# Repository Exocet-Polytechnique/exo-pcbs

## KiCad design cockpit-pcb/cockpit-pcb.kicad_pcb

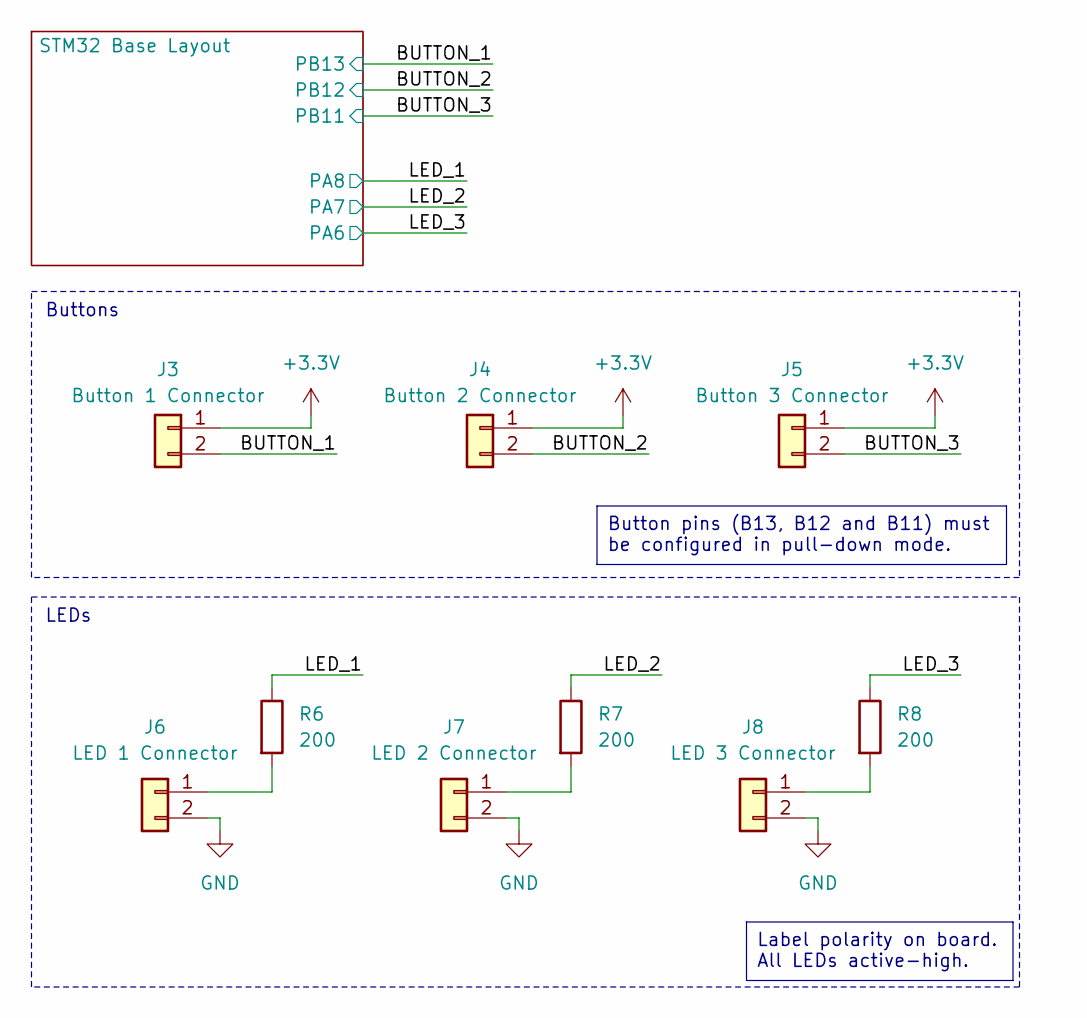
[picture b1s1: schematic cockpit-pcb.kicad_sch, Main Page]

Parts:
J3: Button 1 Connector; JST_ZH_B2B-ZR_1x02_P1.50mm_Vertical; JLCPCB C163033
J4: Button 2 Connector; JST_ZH_B2B-ZR_1x02_P1.50mm_Vertical; JLCPCB C163033
J5: Button 3 Connector; JST_ZH_B2B-ZR_1x02_P1.50mm_Vertical; JLCPCB C163033
J6: LED 1 Connector; JST_PH_B2B-PH-K_1x02_P2.00mm_Vertical; JLCPCB C131337
J7: LED 2 Connector; JST_PH_B2B-PH-K_1x02_P2.00mm_Vertical; JLCPCB C131337
J8: LED 3 Connector; JST_PH_B2B-PH-K_1x02_P2.00mm_Vertical; JLCPCB C131337
R6, R7, R8: 200; R_0603_1608Metric; JLCPCB C8218

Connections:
+3.3V: J3.1, J4.1, J5.1; also elsewhere on the board
/BUTTON_1: J3.2; also elsewhere on the board
/BUTTON_2: J4.2; also elsewhere on the board
/BUTTON_3: J5.2; also elsewhere on the board
/LED_1: R6.1; also elsewhere on the board
/LED_2: R7.1; also elsewhere on the board
/LED_3: R8.1; also elsewhere on the board
GND: J6.2, J7.2, J8.2; also elsewhere on the board
unnamed: J6.1, R6.2
unnamed: J7.1, R7.2
unnamed: J8.1, R8.2

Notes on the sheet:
LEDs
Buttons
Label polarity on board. All LEDs active-high.
Button pins (B13, B12 and B11) must be configured in pull-down mode.

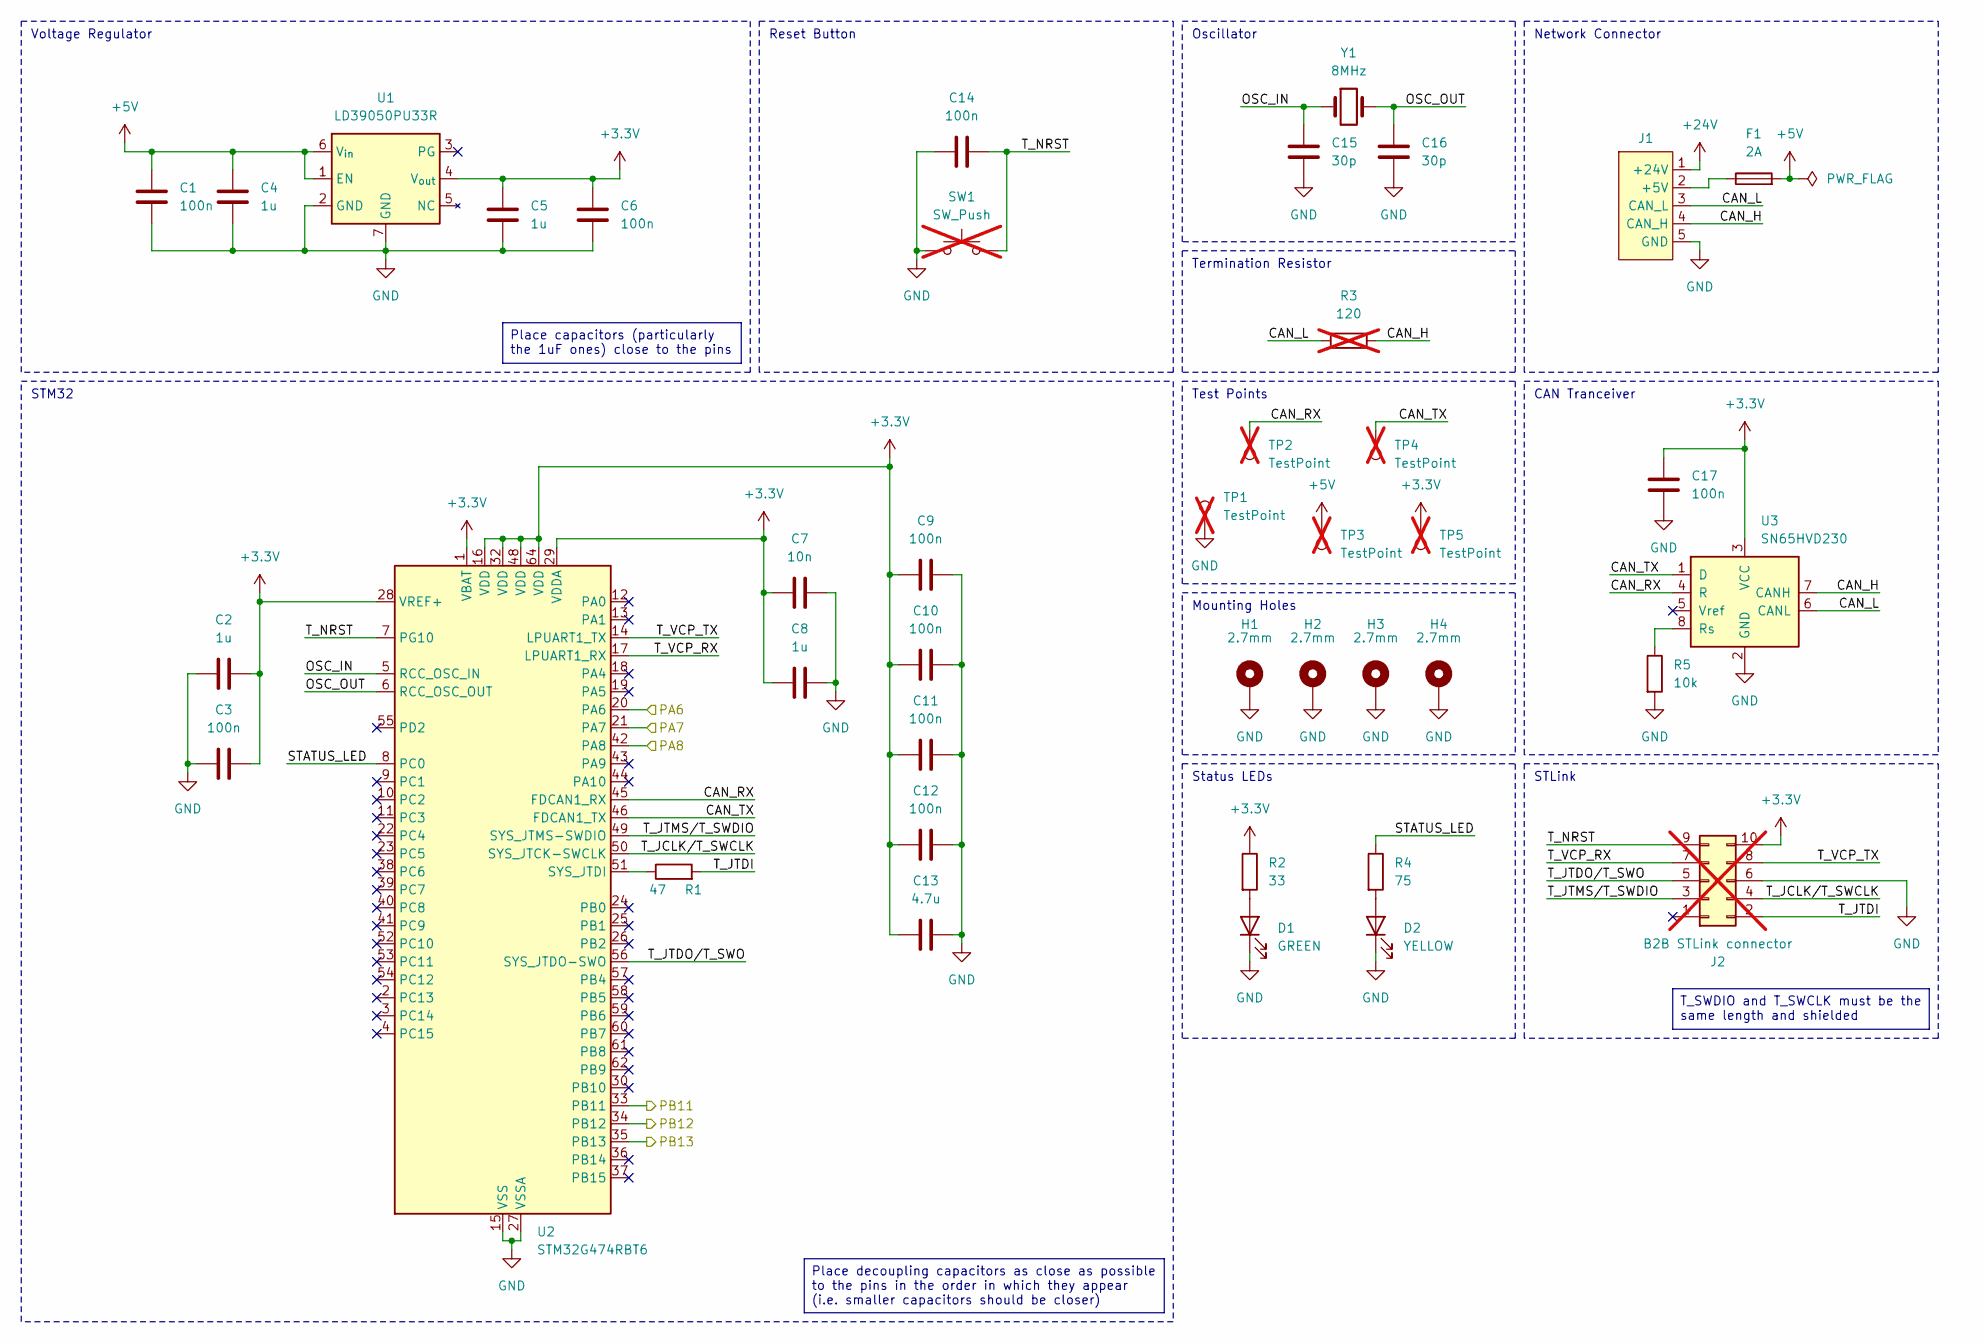
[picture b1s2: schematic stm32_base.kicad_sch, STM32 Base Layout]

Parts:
C1, C3, C6, C9, C10, C11, C12, C14, C17: 100n; C_0402_1005Metric; JLCPCB C1525
C2, C4, C5, C8: 1u; C_0603_1608Metric; JLCPCB C15849
C7: 10n; C_0603_1608Metric; JLCPCB C57112
C13: 4.7u; C_0603_1608Metric; JLCPCB C19666
C15, C16: 30p; C_0603_1608Metric; JLCPCB C1658
D1: GREEN; LED_0805_2012Metric_With_Annotations; JLCPCB C2297
D2: YELLOW; LED_0805_2012Metric_With_Annotations; JLCPCB C2296
F1: 2A; Fuse_Holder_Littelfuse_01530008; JLCPCB C206907
H1, H2, H3, H4: 2.7mm; MountingHole_2.7mm_Pad
J1: Network Connector; Molex_SPOX_5268-05A_1x05_P2.50mm_Horizontal; JLCPCB C185201
J2: B2B STLink connector; AVX 00-9159-010-BTB Connector; not fitted
R1: 47; R_0603_1608Metric; JLCPCB C23182
R2: 33; R_0603_1608Metric; JLCPCB C23140
R3: 120; R_Axial_DIN0309_L9.0mm_D3.2mm_P12.70mm_Horizontal; not fitted
R4: 75; R_0603_1608Metric; JLCPCB C4275
R5: 10k; R_0603_1608Metric; JLCPCB C25804
SW1: SW_Push; SW_PUSH_6mm; not fitted
TP1, TP2, TP3, TP4, TP5: TestPoint; TestPoint_Keystone_5005-5009_Compact; not fitted
U1: LD39050PU33R; DFN-6-1EP_3x3mm_P0.95mm_EP1.7x2.6mm; JLCPCB C132827
U2: STM32G474RBT6; LQFP-64_10x10mm_P0.5mm; JLCPCB C529413
U3: SN65HVD230; SOIC-8_3.9x4.9mm_P1.27mm; JLCPCB C12084
Y1: 8MHz; Crystal_SMD_HC49-SD; Part Name X49SM8MSD2SC; JLCPCB C12674

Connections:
+3.3V: C2.2, C3.2, C5.1, C6.1, C7.1, C8.1, C9.1, C10.1, C11.1, C12.1, C13.1, C17.1, J2.10, R2.1, TP5.1, U1.4 (V_{out}), U2.1 (VBAT), U2.16 (VDD), U2.28 (VREF+), U2.29 (VDDA), U2.32 (VDD), U2.48 (VDD), U2.64 (VDD), U3.3 (VCC); also elsewhere on the board
+5V: C1.1, C4.1, F1.2, TP3.1, U1.1 (EN), U1.6 (V_{in})
+24V: J1.1 (+24V)
/BUTTON_1: U2.35 (PB13); also elsewhere on the board
/BUTTON_2: U2.34 (PB12); also elsewhere on the board
/BUTTON_3: U2.33 (PB11); also elsewhere on the board
/LED_1: U2.42 (PA8); also elsewhere on the board
/LED_2: U2.21 (PA7); also elsewhere on the board
/LED_3: U2.20 (PA6); also elsewhere on the board
/STM32 Base Layout/CAN_H: J1.4 (CAN_H), R3.2, U3.7 (CANH)
/STM32 Base Layout/CAN_L: J1.3 (CAN_L), R3.1, U3.6 (CANL)
/STM32 Base Layout/CAN_RX: TP2.1, U2.45 (FDCAN1_RX), U3.4 (R)
/STM32 Base Layout/CAN_TX: TP4.1, U2.46 (FDCAN1_TX), U3.1 (D)
/STM32 Base Layout/OSC_IN: C15.1, U2.5 (RCC_OSC_IN), Y1.1
/STM32 Base Layout/OSC_OUT: C16.1, U2.6 (RCC_OSC_OUT), Y1.2
/STM32 Base Layout/STATUS_LED: R4.1, U2.8 (PC0)
/STM32 Base Layout/T_JCLK/T_SWCLK: J2.4, U2.50 (SYS_JTCK-SWCLK)
/STM32 Base Layout/T_JTDI: J2.2, R1.2
/STM32 Base Layout/T_JTDO/T_SWO: J2.5, U2.56 (SYS_JTDO-SWO)
/STM32 Base Layout/T_JTMS/T_SWDIO: J2.3, U2.49 (SYS_JTMS-SWDIO)
/STM32 Base Layout/T_NRST: C14.2, J2.9, SW1.2, U2.7 (PG10)
/STM32 Base Layout/T_VCP_RX: J2.7, U2.17 (LPUART1_RX)
/STM32 Base Layout/T_VCP_TX: J2.8, U2.14 (LPUART1_TX)
GND: C1.2, C2.1, C3.1, C4.2, C5.2, C6.2, C7.2, C8.2, C9.2, C10.2, C11.2, C12.2, C13.2, C14.1, C15.2, C16.2, C17.2, D1.1 (K), D2.1 (K), H1.1, H2.1, H3.1, H4.1, J1.5 (GND), J2.6, R5.2, SW1.1, TP1.1, U1.2 (GND), U1.7 (GND), U2.15 (VSS), U2.27 (VSSA), U2.31 (VSS), U2.47 (VSS), U2.63 (VSS), U3.2 (GND); also elsewhere on the board
unnamed: D1.2 (A), R2.2
unnamed: D2.2 (A), R4.2
unnamed: F1.1, J1.2 (+5V)
unnamed: R1.1, U2.51 (SYS_JTDI)
unnamed: R5.1, U3.8 (Rs)

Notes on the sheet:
CAN Tranceiver
Mounting Holes
Voltage Regulator
Reset Button
Status LEDs
Termination Resistor
Oscillator
STLink
Test Points
Network Connector
STM32
T_SWDIO and T_SWCLK must be the same length and shielded
Place capacitors (particularly the 1uF ones) close to the pins
Place decoupling capacitors as close as possible to the pins in the order in which they appear (i.e. smaller capacitors should be closer)

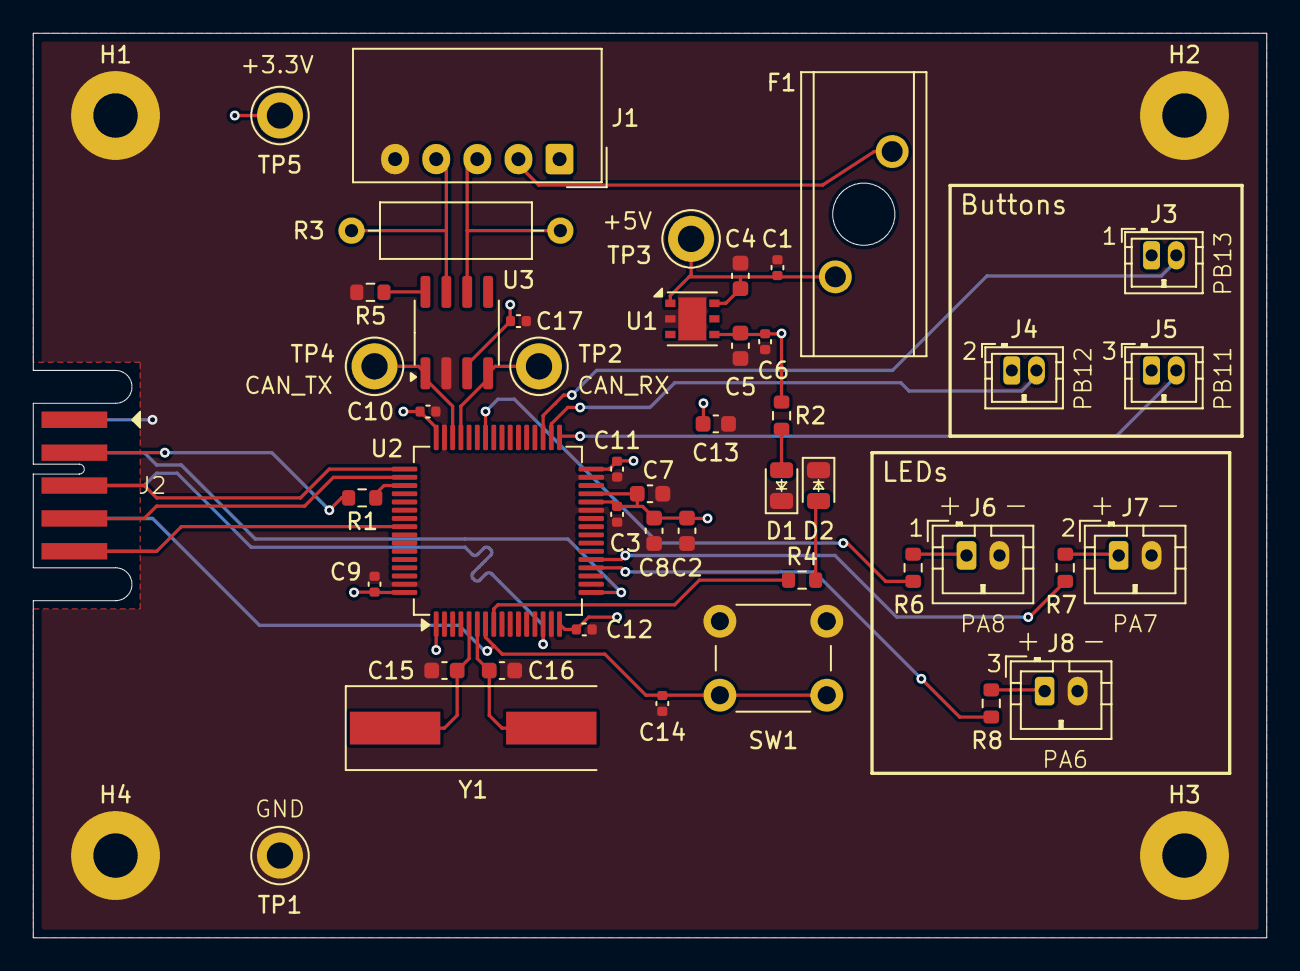
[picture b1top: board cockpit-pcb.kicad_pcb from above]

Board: 2 copper layers, 75.0 x 55.0 mm, 50 parts (0 on the bottom side), 31 nets.
